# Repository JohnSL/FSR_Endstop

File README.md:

FSR_Endstop
===========

Force-Sensitive Resistor controller designed for Delta 3D printers for automatic bed leveling.

## Availability
These circuit boards are now available for purchase from here:

* [Tridprinting.com](http://www.tridprinting.com/Electronics/#3D-Printer-FSR)
* [UltiBots.com](http://www.ultibots.com/fsr-leveling)

You can find my blog post about having these manufactured here: http://trains.socha.com/2014/09/manufacturing-fsr-endstop-controller.html

## History
Back in Februray 2014, Johann modified the Marlin firmware to support force sensitive resistors (FSRs) to allow the firmware to locate the print surface by moving the print nozzle down until the firmware detected that it was touching the bed. FSRs have a very high resistance until you apply pressure, at which point the resistance drops very quickly. You can find more information about his work here: http://reprap.org/wiki/FSR.

I built my own delta printer (http://trains.socha.com/2013/11/building-3dr-simple-delta-printer-part-i.html) and decided to try FSRs. Johann's original branch used one of the thermister inputs, but he later changed to using one of the standard endstop inputs, which I learned when I talked to him at the Seattle Mini Makerfaire. So I tried the endstops.

I had a devel of a time getting it to work. Getting the threshold just right took quite a bit of effort, plus I had to use just the right version of the firmware and get it to load on my Printrboard. It took a little head scratching, and some measurements, to realize that the weight of my glass bed was enough to move the voltage low enough to trigger the end stop. I tried lots of things, and finally used the tape he suggested. That worked better, but I wasn't happy because it was so finiky.

That's how this project got started. I figured it wouldn't be that much effort to use a microcontroller to automatically adjust for the ambient pressure. I'd been wanting to learn how to design and build circuit boards, so my friend Stephen helped me design version 1.0 of this circuit board (in other words, I watched while he layed it out). He also showed me how to hand-solder my first circuit board. You can find more information here:

* [FSR Bed Leveling Trials and Tribulations](http://trains.socha.com/2014/05/fsr-bed-leveling-trials-and-tribulations.html?showComment=1400160705176)
* [Auto Adjust FSR End Stop Detector](http://trains.socha.com/2014/05/auto-adjust-fsr-end-stop-detector.html?showComment=1399251889736)
* [Building the FSR Circuit Boards](http://trains.socha.com/2014/07/building-fsr-circuit-boards.html)

## FSR Endstop Controller
Although not a clever name, it certainly describes what this board does. To use the board, you connect a cable to the endstop on your printer board, and then you connect three FSRs to the inputs of the board. And that's it. The board receives power from the printer board and automatically adjusts to the ambient pressure on the sensors. Whenever the head hits the build plate, the board will detect this and trigger the end stop.

To date, we've made two different versions of the board. Revision 1.1 is shown on the left, and 1.2 is on the right:

The difference between these two is the arrangement of pins that can be used to modify the behavior of the board. In the revision 1.1 board, these pins are labeld IO1, IO2, and IO3. While the same pins are labeled SN2, SN1, and NC on the revision 1.2 boards. Additionally, the 1.2 boards allow you to solder in a 2 by 3 array of header pins and then use jumpers to connect any combination of these three pins to ground (GND), whereas the 1.1 boards require using wires to connect any combination of these pins to GND.

### Wiring the Endstop
Use a three-wire cable to connect the endstop on your printer board to this circuit board. These should be connected to the three pins labeled "+/-", "+/-", and "SIG" in the upper-left corner of the image above. On all the printer boards I've looked at, the signal wire is on the outside. The 5V connection is either on the middle pin or the outside pin. You'll want to check your printer board to ensure you attach the connector with the correct orientation.

### Setting the Sensitivity
There are two jumpers  you can use to modify the sensitivy of this board. By default (no jumpers), the force much be such that the voltage drops below 0.92 of the ambient value before the output is triggered. Each FSR is monitored independently of the others, so the output will trigger when at least one FSR triggers an input. In the table below, GND means you've connected that pin to ground.

| SN1 / IO2 | SN2 / IO1 | Sensitivity |
|-----------|-----------|-------------|
| GND | GND | 0.8 |
| GND |  -  | 0.85 |
|  -  | GND | 0.95 |
|  -  |  -  | 0.92 |

### Setting NC/NO Behavior
By default, the end stop output will be normally open (NO), which should work fine with any printer. However if you want to change this to normally closed (NC), connect pin NC/IO3 to GND.

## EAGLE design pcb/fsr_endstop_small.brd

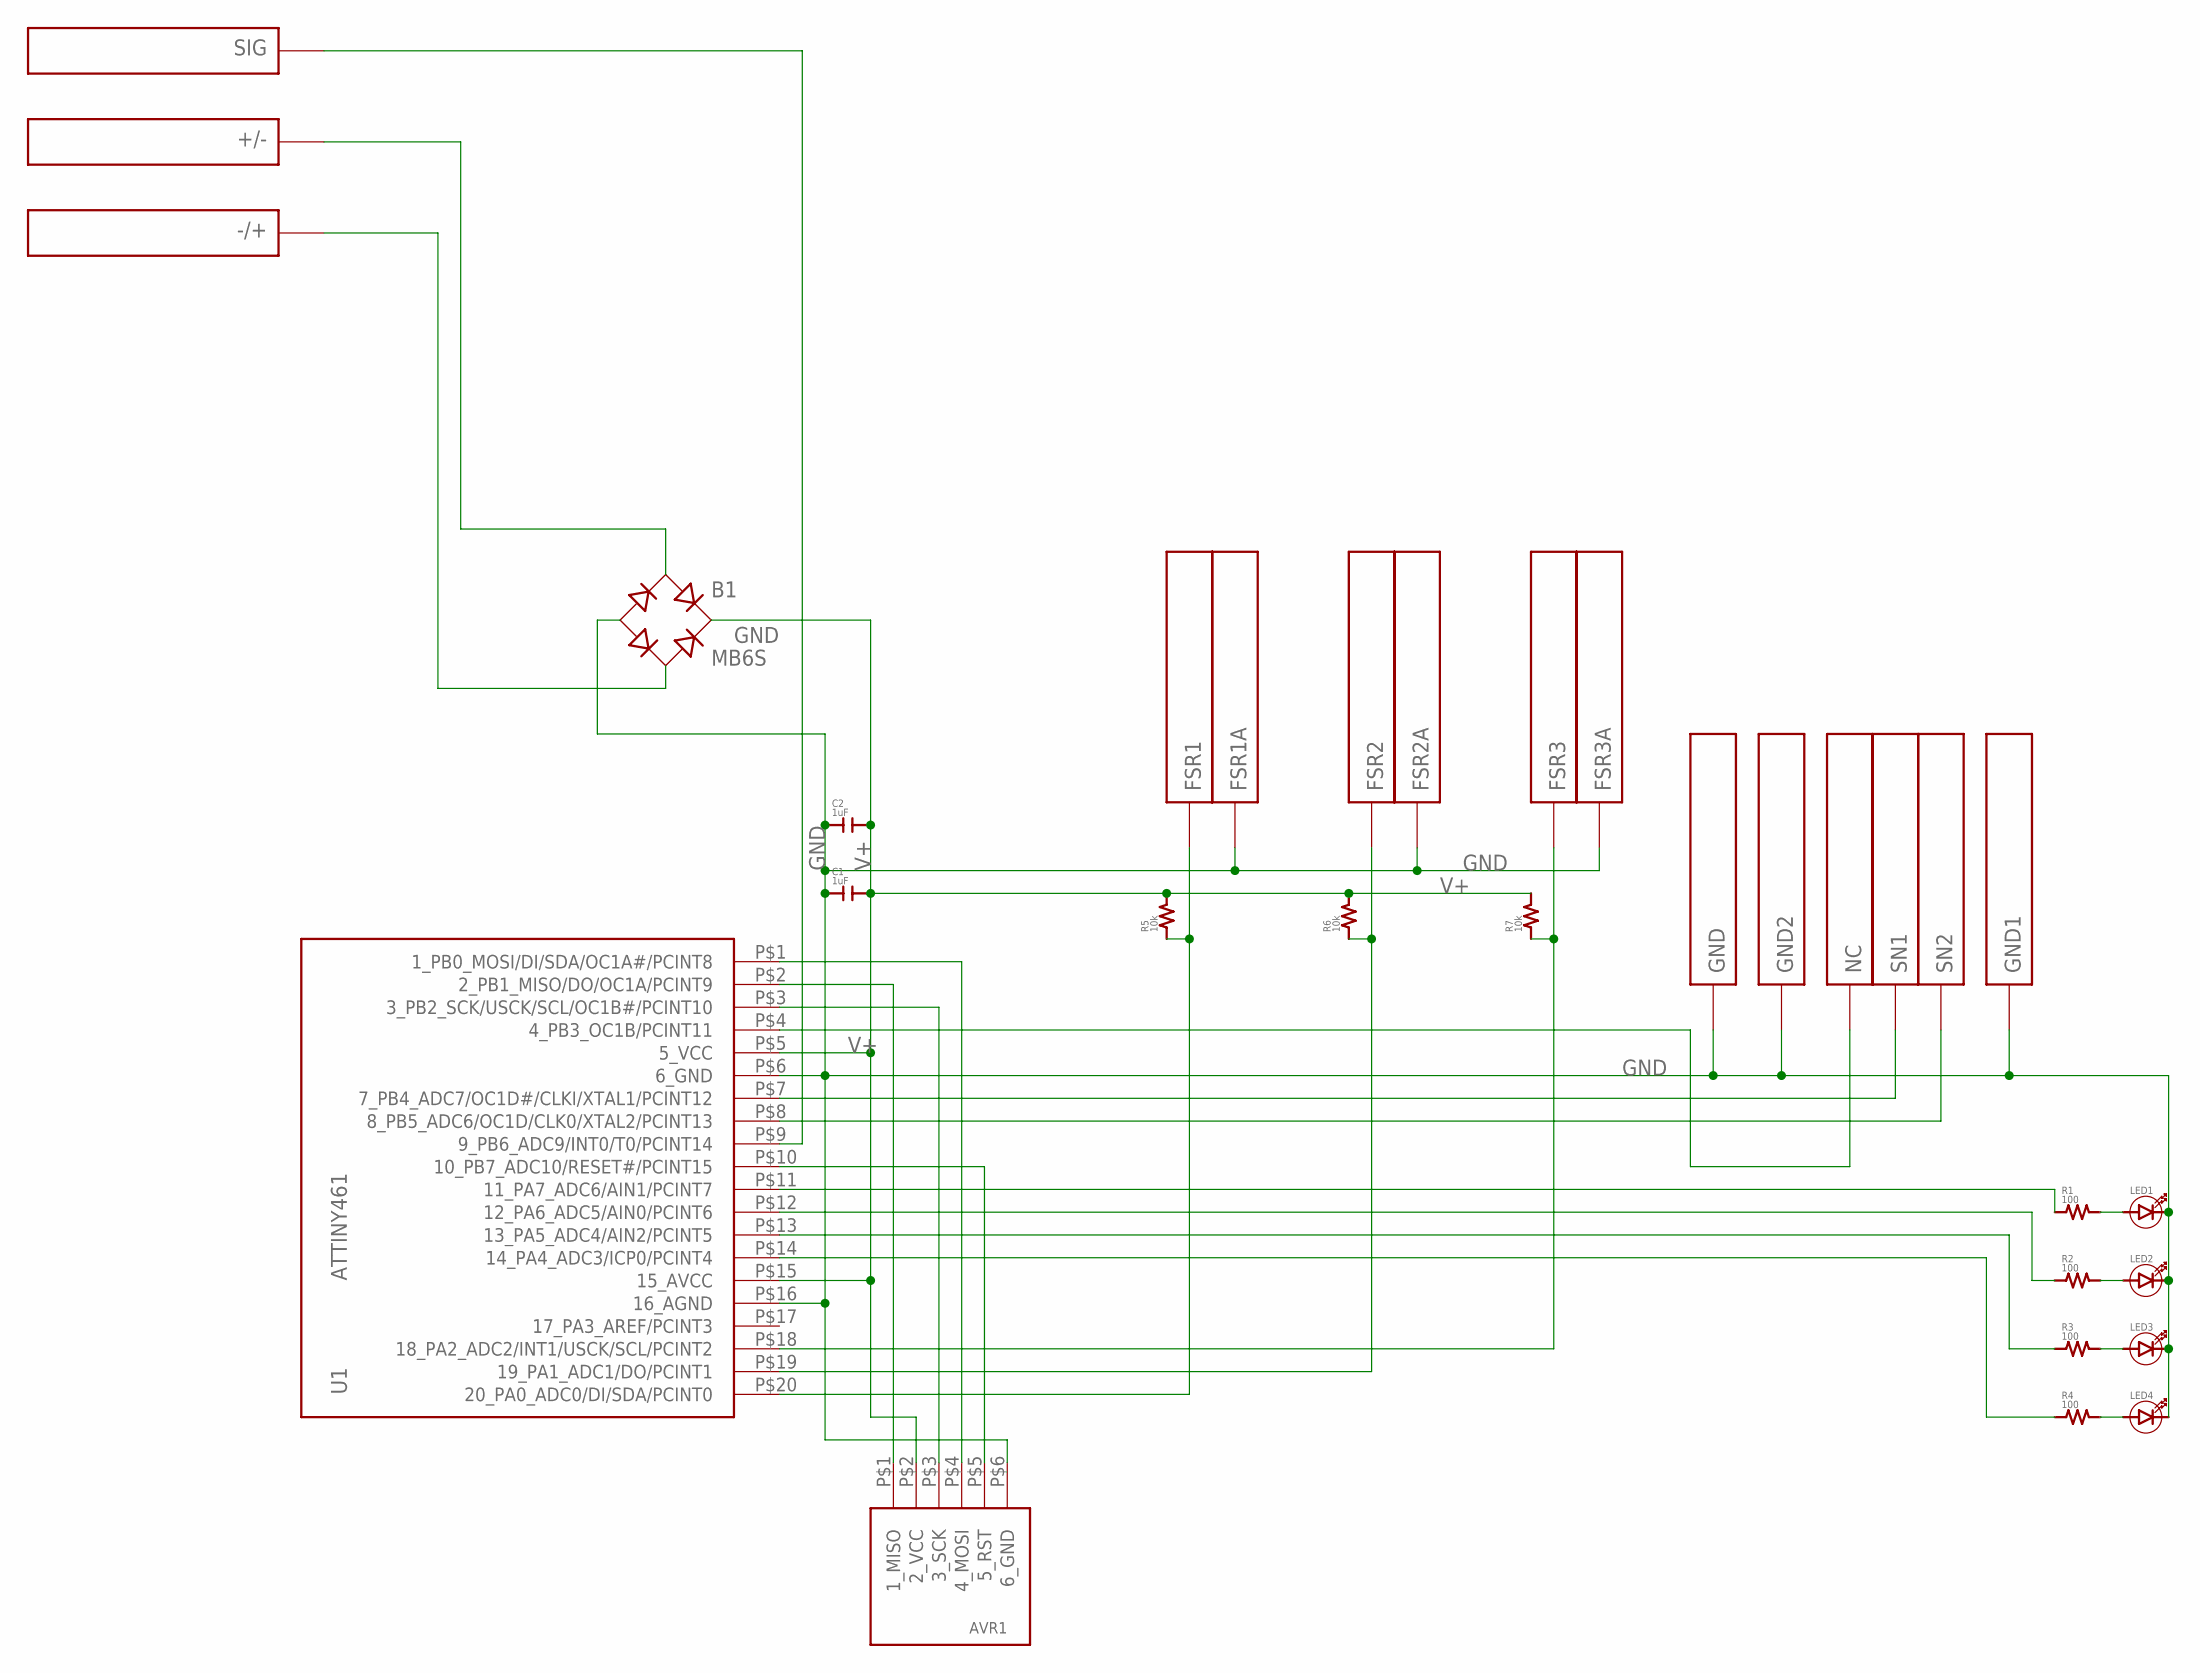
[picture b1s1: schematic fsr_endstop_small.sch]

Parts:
+/-: PIN1.2MM; PIN_1.2MM
-/+: PIN1.2MM; PIN_1.2MM
AVR1: AVR6
B1: MB6S; SOIC-4
C1, C2: 1uF; 0603
FSR1, FSR1A, FSR2, FSR2A, FSR3, FSR3A: PIN1.2MM; PIN_1.2MM
GND, GND1, GND2: PIN1.2MM; PIN_1.2MM
LED1, LED2, LED3, LED4: LED0603; 0603_DIODE
NC: PIN1.2MM; PIN_1.2MM
R1, R2, R3, R4: 100; 0603
R5, R6, R7: 10k; 0603
SIG: PIN1.2MM; PIN_1.2MM
SN1, SN2: PIN1.2MM; PIN_1.2MM
U1: ATTINY461; SOIC-20

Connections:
GND: AVR1.P$6 (6_GND), B1.-, C1.1, C2.1, FSR1A.P$1, FSR2A.P$1, FSR3A.P$1, GND.P$1, GND1.P$1, GND2.P$1, LED1.-, LED2.-, LED3.-, LED4.-, U1.P$6 (6_GND), U1.P$16 (16_AGND)
unnamed: AVR1.P$4 (4_MOSI), U1.P$1 (1_PB0_MOSI/DI/SDA/OC1A#/PCINT8)
unnamed: AVR1.P$1 (1_MISO), U1.P$2 (2_PB1_MISO/DO/OC1A/PCINT9)
unnamed: -/+.P$1, B1.~2 (AC2)
unnamed: +/-.P$1, B1.~1 (AC1)
unnamed: AVR1.P$3 (3_SCK), U1.P$3 (3_PB2_SCK/USCK/SCL/OC1B#/PCINT10)
unnamed: AVR1.P$5 (5_RST), U1.P$10 (10_PB7_ADC10/RESET#/PCINT15)
unnamed: FSR1.P$1, R5.1, U1.P$20 (20_PA0_ADC0/DI/SDA/PCINT0)
unnamed: FSR2.P$1, R6.1, U1.P$19 (19_PA1_ADC1/DO/PCINT1)
unnamed: FSR3.P$1, R7.1, U1.P$18 (18_PA2_ADC2/INT1/USCK/SCL/PCINT2)
unnamed: R4.1, U1.P$14 (14_PA4_ADC3/ICP0/PCINT4)
unnamed: R3.1, U1.P$13 (13_PA5_ADC4/AIN2/PCINT5)
unnamed: R2.1, U1.P$12 (12_PA6_ADC5/AIN0/PCINT6)
unnamed: R1.1, U1.P$11 (11_PA7_ADC6/AIN1/PCINT7)
unnamed: SIG.P$1, U1.P$9 (9_PB6_ADC9/INT0/T0/PCINT14)
unnamed: NC.P$1, U1.P$4 (4_PB3_OC1B/PCINT11)
unnamed: SN2.P$1, U1.P$8 (8_PB5_ADC6/OC1D/CLK0/XTAL2/PCINT13)
unnamed: SN1.P$1, U1.P$7 (7_PB4_ADC7/OC1D#/CLKI/XTAL1/PCINT12)
unnamed: LED1.+, R1.2
unnamed: LED2.+, R2.2
unnamed: LED3.+, R3.2
unnamed: LED4.+, R4.2
V+: AVR1.P$2 (2_VCC), B1.+, C1.2, C2.2, R5.2, R6.2, R7.2, U1.P$5 (5_VCC), U1.P$15 (15_AVCC)

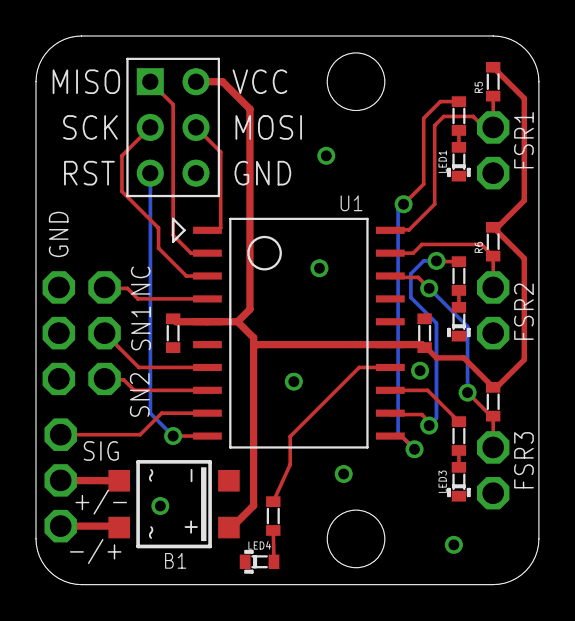
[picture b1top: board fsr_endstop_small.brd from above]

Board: 2 copper layers, 27.9 x 30.5 mm, 32 parts (1 on the bottom side), 23 nets.

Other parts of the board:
U$1: OSHW-LOGO-M

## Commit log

2014-04-06 Initial schematic commit
2014-04-06 Schematic first rev complete
2014-04-06 Finished first component placement
2014-04-06 Packed components in tighter
2014-04-06 Completed routing
2014-04-06 Added ground plane, final 1 layer board.
2014-04-06 Initial component placement for smaller 2-layer board
2014-04-06 Completed non-GND routing
2014-04-06 Added ground plane, done with small version
2014-04-06 Cleanedup silkscreen, added board name to back
2014-04-08 Moving PCB design files to subdirectory
2014-04-27 Initial check-in of the source. This handles only a single FSR.
2014-04-27 Now have all three FSR inputs working.
2014-04-27 Fixed problem with FSR3 staying triggered.
2014-04-27 Added tiggered LED support
2014-04-28 Reverse polarity of diodes
    Diodes were backwards in the schematic for the bridge rectifier.
2014-04-30 Added NC output.
2014-05-03 Adding missing trace between LED4 and R4
2014-05-03 Replaced the discrete diodes with a bridge rectifier chip for easier hand soldering.
2014-05-13 Made various fixes to the 1.1 version.
2014-05-16 Adding Trinket/ATtiny85 version of the file
2014-06-16 After sending to DFRobot, using their design rules file.
2014-06-29 Revision 1.2 includes three jumpers for modifying settings.
2014-06-29 Change the threshold from 0.92 to 0.85, and also cleaned up the code a little.
2014-06-29 Added support for jumpers to change between NC and NO, and also to change sensitivity.
2014-07-13 Moved the trigger check outside of the short sample loop so the variance in trigger times will be less, and triggers will be faster, on average.
2014-07-13 The first version of the firmware on shipping boards.
2014-07-13 This version has improved reaction time as a result of moving the trigger checkout outside of the loop used to upate the short sample array.
2014-07-13 Adding image to use in readme.
2014-07-20 Now blink the red LEDs during startup to indicate the firmware version
2014-07-25 Update FSR_Detector.ino
    Support multi-sensor FSR. For square beds better to have 4 sensors.
2014-09-21 Update README.md
    Added link to Tridprinting.com.
2015-10-10 Adding Ultibots

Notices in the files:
parts and their libraries:
SparkFun-Aesthetics: Licensing: Creative Commons ShareAlike 4.0 International - https://creativecommons.org/licenses/by-sa/4.0
